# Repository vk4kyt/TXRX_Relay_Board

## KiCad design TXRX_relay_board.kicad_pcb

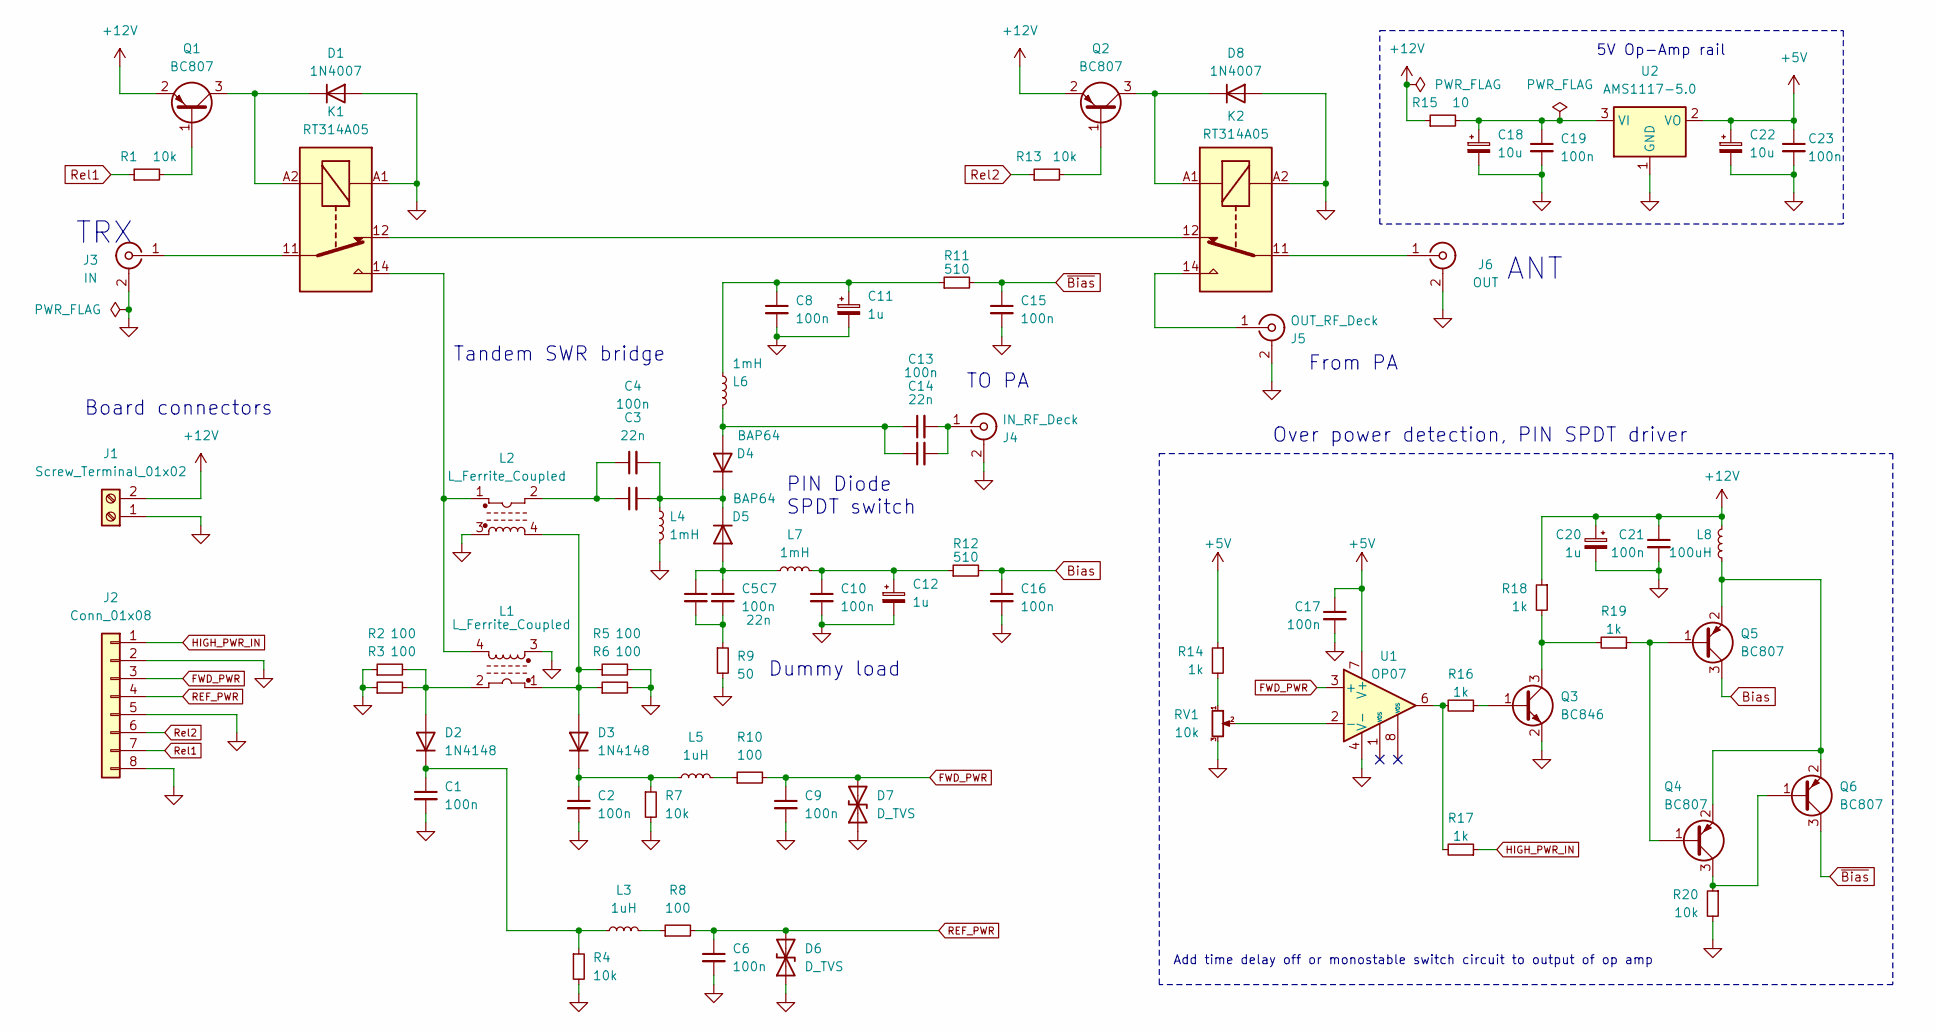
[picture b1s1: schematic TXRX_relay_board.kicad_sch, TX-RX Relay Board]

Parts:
C1, C2, C8, C9, C10, C15, C16, C17, C19, C21, C23: 100n; C_0603_1608Metric_Pad1.08x0.95mm_HandSolder; Ratings 100V; MPN MLASH168SB7104KTNA01
C3, C5, C14: 22n; C_0805_2012Metric_Pad1.18x1.45mm_HandSolder; Ratings 100V; MPN C0805C223M1RACAUTO
C4, C7, C13: 100n; C_0805_2012Metric_Pad1.18x1.45mm_HandSolder; Ratings 100V; MPN 08051C104KAT4A
C6: 100n; C_0603_1608Metric_Pad1.08x0.95mm_HandSolder; Ratings 100V; MPN 08051C104KAT4A
C11, C12, C20: 1u; C_0805_2012Metric_Pad1.18x1.45mm_HandSolder; Ratings 100V; MPN HMR212CC7105KG-T
C18, C22: 10u; C_0805_2012Metric_Pad1.18x1.45mm_HandSolder; Ratings 100V; MPN KGM21AR71C106MU
D1, D8: 1N4007; D_SMA; MPN MRA4007T3G
D2, D3: 1N4148; D_SOD-123F; MPN 1N4148W-G3-08
D4, D5: BAP64; D_SOD-323_HandSoldering; MPN BAP64-03,115
D6, D7: D_TVS; D_0805_2012Metric_Pad1.15x1.40mm_HandSolder; Ratings 30v; MPN EZA-EGCA50AV
J1: Screw_Terminal_01x02; TerminalBlock_bornier-2_P5.08mm; MPN 1548128
J2: Conn_01x08; JST_EH_B8B-EH-A_1x08_P2.50mm_Vertical; MPN B8B-EH-A(LF)(SN)(P)
J3: IN; SMA_Amphenol_901-144_Vertical; MPN 901-144-8RFX
J4: IN_RF_Deck; SMA_Amphenol_901-144_Vertical; MPN 901-144-8RFX
J5: OUT_RF_Deck; Coax_solder
J6: OUT; Coax_solder
K1, K2: RT314A05; Relay_SPDT_Schrack-RT1-16A-FormC_RM5mm; MPN RT314A05
L1: L_Ferrite_Coupled; FT82-61_trafo; Ratings N>=15; MPN 5961000601
L2: L_Ferrite_Coupled; FT50-61_trafo; Ratings N>=15; MPN 5961000301
L3, L5: 1uH; L_0603_1608Metric_Pad1.05x0.95mm_HandSolder; MPN ILSB0603ERR10K
L4, L6, L7: 1mH; L_1812_4532Metric_Pad1.30x3.40mm_HandSolder; Ratings 100V; MPN ISC1812ER102K
L8: 100uH; L_1206_3216Metric; MPN ILSB1206ER1R0K
Q1, Q2, Q4, Q5, Q6: BC807; SOT-23; MPN BC807-40-QVL
Q3: BC846; SOT-23; MPN BC846A
R1, R4, R7, R13, R20: 10k; R_0603_1608Metric_Pad0.98x0.95mm_HandSolder; MPN RK73H1JTTDD1001F
R2, R3, R5, R6: 100; R_2010_5025Metric_Pad1.40x2.65mm_HandSolder; MPN RMC1/2-101JTE
R8, R10: 100; R_0603_1608Metric_Pad0.98x0.95mm_HandSolder; MPN CRG0603F100R
R9: 50; SMA_Amphenol_901-144_Vertical; Ratings Dummy Load; MPN 901-144-8RFX
R11, R12: 510; R_1206_3216Metric_Pad1.30x1.75mm_HandSolder; MPN AC0603FR-07510RL
R14, R16, R17, R18, R19: 1k; R_0603_1608Metric_Pad0.98x0.95mm_HandSolder; MPN RK73H1JTTDD1001F
R15: 10; R_2010_5025Metric_Pad1.40x2.65mm_HandSolder; Ratings 1.5W; MPN RNCL2010FT10R0
RV1: 10k; Potentiometer_Bourns_3296W_Vertical; MPN 3296W-1-103
U1: OP07; SOIC-8_3.9x4.9mm_P1.27mm; MPN OP-07DPSR
U2: AMS1117-5.0; SOT-223-3_TabPin2; MPN LM1117MPX-5.0/NOPB

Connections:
+5V: C17.1, C22.1, C23.1, R14.1, U1.7 (V+), U2.2 (VO)
+12V: C20.1, C21.1, J1.2, L8.1, Q1.2 (E), Q2.2 (E), R15.1, R18.1
Bias: C16.1, Q5.3 (C), R12.2
FWD_PWR: C9.1, D7.2 (A2), J2.3, R10.2, U1.3 (+)
GND: C1.2, C2.2, C6.2, C8.2, C9.2, C10.2, C11.2, C12.2, C15.2, C16.2, C17.2, C18.2, C19.2, C20.2, C21.2, C22.2, C23.2, D1.2 (A), D6.1 (A1), D7.1 (A1), D8.2 (A), J1.1, J2.2, J2.5, J2.8, J3.2 (Ext), J4.2 (Ext), J5.2 (Ext), J6.2 (Ext), K1.A1, K2.A2, L1.3, L2.3, L4.2, Q3.2 (E), R2.1, R3.1, R4.2, R5.2, R6.2, R7.2, R9.2, R20.2, RV1.3, U1.4 (V-), U2.1 (GND)
HIGH_PWR_IN: J2.1, R17.1
unnamed: C3.1, C4.1, L2.2
unnamed: C5.2, C7.2, R9.1
unnamed: C10.1, C12.1, L7.2, R12.1
unnamed: C8.1, C11.1, L6.1, R11.1
unnamed: D1.1 (K), K1.A2, Q1.3 (C)
unnamed: D2.2 (A), L1.2, R2.2, R3.2
unnamed: C1.1, D2.1 (K), L3.1, R4.1
unnamed: D3.2 (A), L1.1, L2.4, R5.1, R6.1
unnamed: C2.1, D3.1 (K), L5.1, R7.1
unnamed: C13.1, C14.1, D4.2 (A), L6.2
unnamed: C3.2, C4.2, D4.1 (K), D5.1 (K), L4.1
unnamed: C5.1, C7.1, D5.2 (A), L7.1
unnamed: D8.1 (K), K2.A1, Q2.3 (C)
unnamed: J3.1 (In), K1.11
unnamed: C13.2, C14.2, J4.1 (In)
unnamed: J5.1 (In), K2.14
unnamed: J6.1 (In), K2.11
unnamed: K1.12, K2.12
unnamed: K1.14, L1.4, L2.1
unnamed: L3.2, R8.1
unnamed: L5.2, R10.1
unnamed: Q1.1 (B), R1.2
unnamed: Q2.1 (B), R13.2
unnamed: Q3.1 (B), R16.1
unnamed: Q3.3 (C), R18.2, R19.2
unnamed: Q4.1 (B), Q5.1 (B), R19.1
unnamed: Q4.3 (C), Q6.1 (B), R20.1
unnamed: L8.2, Q4.2 (E), Q5.2 (E), Q6.2 (E)
unnamed: R14.2, RV1.1
unnamed: R16.2, R17.2, U1.6
unnamed: RV1.2, U1.2 (-)
unnamed: C18.1, C19.1, R15.2, U2.3 (VI)
REF_PWR: C6.1, D6.2 (A2), J2.4, R8.2
Rel1: J2.7, R1.1
Rel2: J2.6, R13.1
~Bias: C15.1, Q6.3 (C), R11.2

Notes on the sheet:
Board connectors
5V Op-Amp rail
From PA
TRX
ANT
Dummy load
TO PA
PIN Diode SPDT switch
Tandem SWR bridge
Add time delay off or monostable switch circuit to output of op amp
Over power detection, PIN SPDT driver

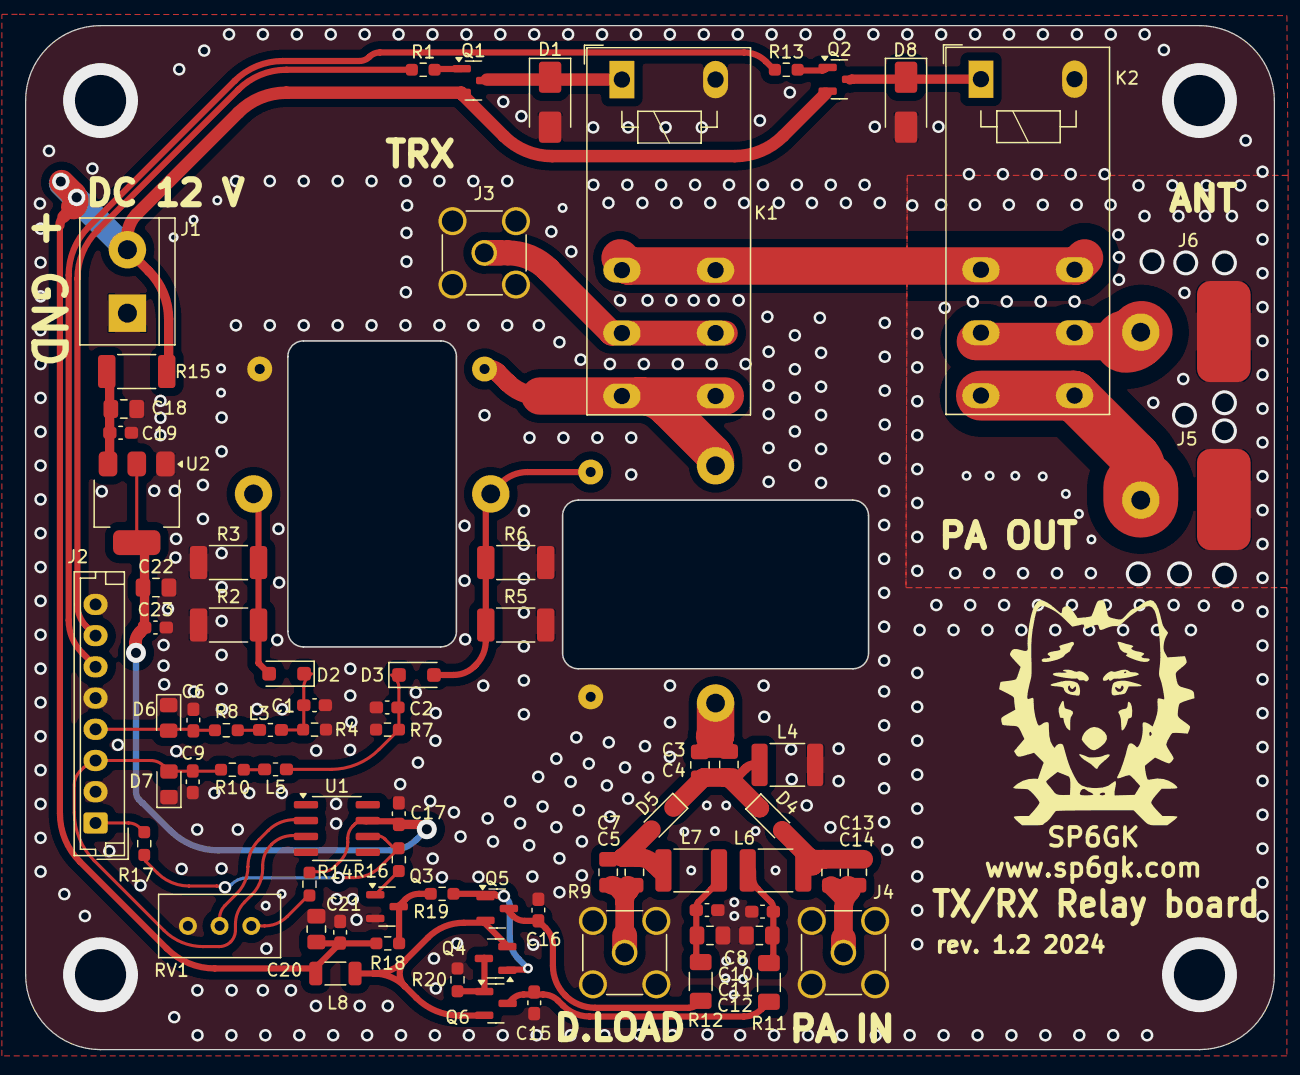
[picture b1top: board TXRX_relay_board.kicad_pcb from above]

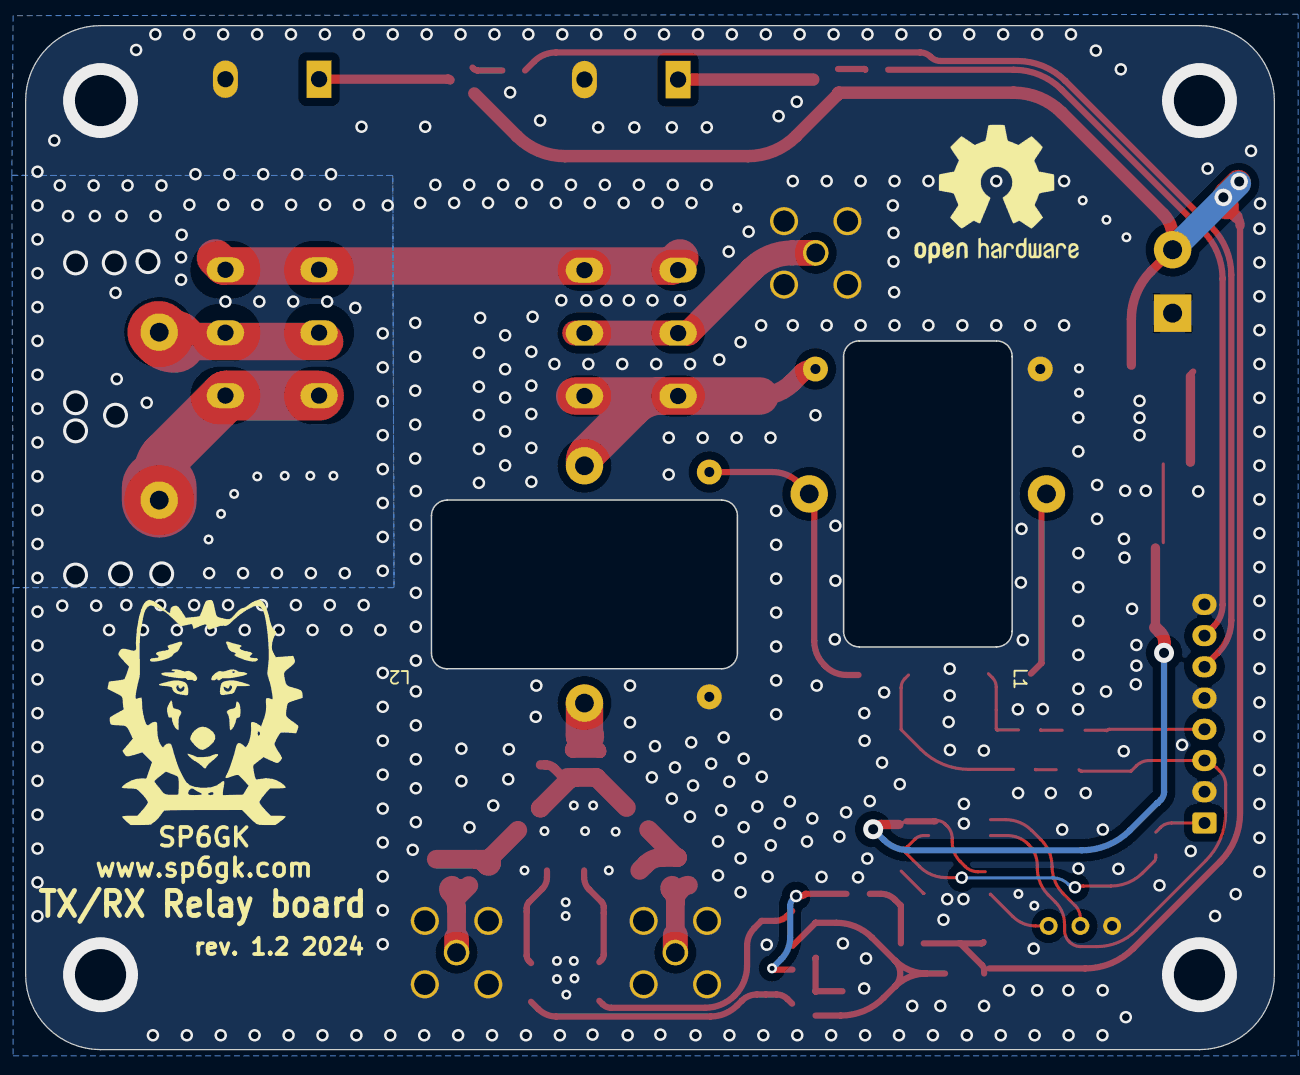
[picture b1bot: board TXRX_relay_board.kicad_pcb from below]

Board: 2 copper layers, 100.0 x 82.0 mm, 77 parts (3 on the bottom side), 42 nets.

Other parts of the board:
OSHW: OSHW-Logo2_14.6x12mm_SilkScreen

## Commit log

2024-09-11 Used ERC to fix minor Errors
    Used the ERC to fix minor error and warnings. Some relegated to "Excluded"
2024-09-11 DRC Update
    Design checked using DRC
2024-09-14 Ready to Order
    Minor updates in preparation to order PCBs and components
2024-09-26 All checks done, BOM updated
    All ERC and DRC checks have been run, and erros and or warnings resolved.
    BOM fully updated with Manufacturer part numbers (MPN) ready for order placement
